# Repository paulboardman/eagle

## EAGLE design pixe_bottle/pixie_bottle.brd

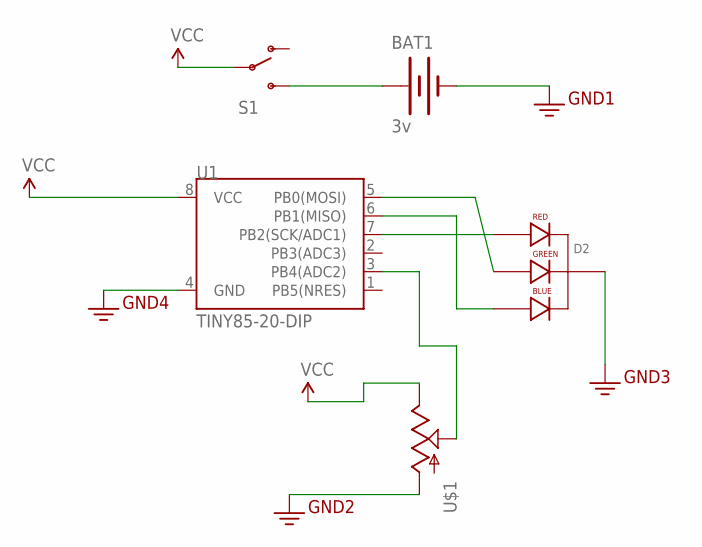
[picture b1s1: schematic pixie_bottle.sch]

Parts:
BAT1: 3v; BATTCOM_20MM_PTH
D2: LED-RGB-CC-THRUDIFFUSE; LED-RGB-THRU
S1: SWITCH-SPDTPTH; SWITCH-SPDT
U1: TINY85-20-DIP; DIP08
U$1: POT-RV16AF-20; POT_ALPHA_RV16AF-20

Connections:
3.3V: BAT1.2 (-), D2.2 (CATHODE), U1.4 (GND), U$1.1 (A)
unnamed: D2.1 (RED_CATHODE), U1.7 (PB2(SCK/ADC1))
unnamed: D2.3 (GREEN_CATHODE), U1.5 (PB0(MOSI))
unnamed: D2.4 (BLUE_CATHODE), U1.6 (PB1(MISO))
unnamed: U1.3 (PB4(ADC2)), U$1.2 (S)
unnamed: BAT1.1 (+), S1.3 (S)
VCC: S1.2, U1.8 (VCC), U$1.3 (E)

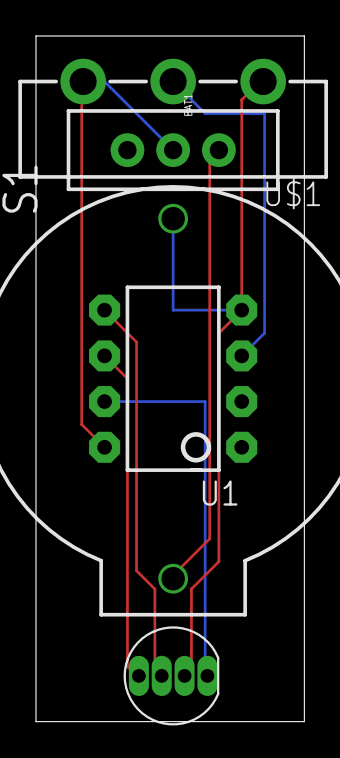
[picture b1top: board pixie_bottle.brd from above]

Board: 2 copper layers, 14.9 x 38.1 mm, 5 parts (0 on the bottom side), 7 nets.

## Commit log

2014-02-23 first post
2023-06-04 testing out KiKad (7.0) instead of Eagle

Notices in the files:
parts and their libraries:
SparkFun-Electromechanical: Licensing: CC v3.0 Share-Alike You are welcome to use this library for commercial purposes.
